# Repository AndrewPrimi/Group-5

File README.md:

# Electronics Tool Bench – Group 5

This repository is used to store coursework, scripts, and supporting materials for our electronics and embedded systems projects throughout the semester. It includes work completed using tools such as the Raspberry Pi and GitHub for collaborative development.

## Course Deliverables
 - Documentaton under Technical_Documenation Folder
 - User Manual under User_Manual folder
 - Current Status of these files are relevant to the status of the completion of the project, these files updated with every deliverable and checkpoint

### Deliverable 2 – Raspberry Pi Hello World (RP4)
- File(s): HelloWorldPI.py, HelloWorldScripts
- Description: Python script used to verify Raspberry Pi setup and GitHub integration. The script was run successfully on the Raspberry Pi as part of the assignment. Practice GitHub Commit files. 

### Deiverable 3 - DigiPot and Rotary Encoder
- File(s): gpio_status.py, gpio_status_simple.py, potentiometer.py, LED_ON_OFF.py
- Description: Scripts used to setup GPIO ports and to use the digital potentiometer (change resistance) and rotary encoder (turn off/on an LED), LED turn off and on script.

### Deliverable 4 – Power Supply Simulation, CAD, GPIO Diagram and Power Diagram
- File(s): Deliverable_4.pdf, KiCad_Files, Multisim_Schematics
- Description: GPIO and power diagrams, ±12 V power supply simulation, and initial PCB CAD design using KiCad for future Pi-HAT development.

### Deliverable 5 – Checkpoint C (DigiPot User Interface)  
- File(s): Checkpoint_C_Code (name your Checkpoint “C” code clearly), updated weekly documentation + demo video
- Description: Rotary encoder + LCD user interface to set and display digipot resistance. Slow spin adjusts by 10 Ω and fast spin adjusts by 100 Ω, with a selectable range of 100 Ω to 10 kΩ. Pressing the encoder selects/sets the value and programs the digipot (verified with a multimeter). The UI must allow selecting which side of the dual digipot is being controlled and each side must be independent. Holding the knob for 3 seconds returns to the primary selection screen. No LCD buttons are used and the system should not reboot between resistance changes.

### Deliverable 6 – ±12 V Supply Under Load, 5-bit ADC Simulation, and PCB Schematic Updates
- File(s): Deliverable_6.pdf, KiCad_Files, Multisim_Schematics, updated weekly documentation
- Description: Updated and validated the split-rail ±12 V power supply to ensure stability with no load and with an approximate 50 mA load on both rails. Documented and clarified system ground/reference behavior, including the virtual ground midpoint concept. Developed and simulated a 5-bit-equivalent ADC design using a SAR-based approach with an R-2R DAC, sample-and-hold circuit, and LM339 comparator. Updated the Pi-Hat protector KiCad schematic/PCB to include the ±12 V supply nets (+12 V, GND, −12 V), ADC routing concepts, and initial layout/routing screenshots with key design decisions and debugging considerations (labels, test points, footprints).

### Deliverable 7 – Physical ADC, Ohmmeter, Voltmeter
- File(s): N/A
- Description: 
  
Additional deliverables will be added to this repository as the semester progresses.

## Group Members
- Andrew Primiano  
- Logan Griffy  
- Tillman Clark  
- George Braun
- Kai DeVito

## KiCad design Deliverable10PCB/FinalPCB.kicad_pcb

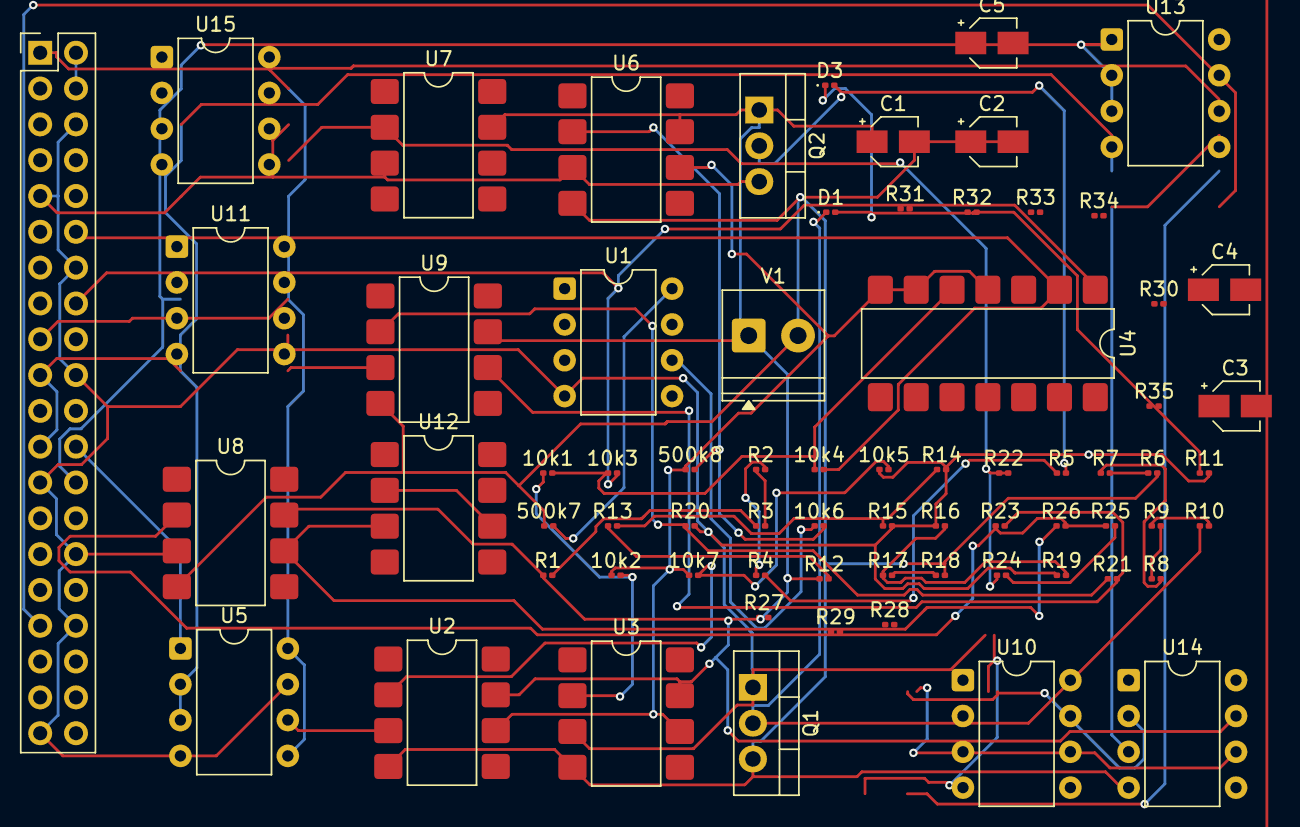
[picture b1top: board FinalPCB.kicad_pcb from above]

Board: 2 copper layers, 70 parts (0 on the bottom side), 53 nets.

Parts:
10k1, 10k2, 10k3, 10k4, 10k5, 10k6, 10k7, 500k7: R; R_0201_0603Metric
500k8: R_Measure; R_0201_0603Metric
C1, C2: 0.0000001; CP_Elec_3x5.3
C3: 470uF; CP_Elec_3x5.3
C4, C5: 10nf; CP_Elec_3x5.3
D1, D3: D; D_0201_0603Metric
J2: PiHeaderM; PinHeader_2x20_P2.54mm_Vertical
Q1: NMOS; TO-220-3_Vertical
Q2: PMOS; TO-220-3_Vertical
R1, R2, R3, R4, R5, R6, R7, R8, R9, R10, R11, R12, R13, R14, R15, R16, R17, R18, R19: 100; R_0201_0603Metric
R20, R22, R23, R25, R26, R28: 10k; R_0201_0603Metric
R21: 20k; R_0201_0603Metric
R24: 30k; R_0201_0603Metric
R27, R31, R32, R33, R34: 100k; R_0201_0603Metric
R29: 70k; R_0201_0603Metric
R30, R35: 220k; R_0201_0603Metric
U1, U5, U13: MCP4131-xxxx-P; DIP-8_W7.62mm
U2, U3, U6, U7, U8, U9, U12: LM741; SMDIP-8_W7.62mm
U4: LM339; SMDIP-14_W7.62mm
U10, U11, U14: TL081; DIP-8_W7.62mm
U15: MCP4231-103E_P; DIP-8_W7.62mm
V1: 24; TerminalBlock_Phoenix_PT-1,5-2-3.5-H_1x02_P3.50mm_Horizontal

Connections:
+3.3V: 10k1.2, U4.5 (+)
+12V: C1.1, Q2.1 (D), R1.1, R12.1, U2.7 (V+), U3.7 (V+), U6.7 (V+), U7.7 (V+), U8.7 (V+), U9.7 (V+), U10.7 (V+), U11.7 (V+), U14.7 (V+), V1.1
-12V: 500k7.1, C1.2, C2.1, C2.2, Q1.3 (S), R6.2, R18.2, U2.4 (V-), U3.4 (V-), U6.4 (V-), U8.4 (V-), U9.4 (V-), U10.4 (V-), U11.4 (V-), U14.4 (V-), V1.2
/3.3V: 10k3.1, 10k4.1, J2.1, J2.17, U13.5 (P0A), U13.8 (V_{DD}), U15.7 (P1A), U15.8 (P0A)
/5V: J2.2, J2.4
/CE0: J2.24, U13.1 (~CS), U15.1 (~CS)
/CE1: J2.26, U1.1 (~CS), U5.1 (~CS)
/GND*GPIO: J2.6, J2.9, J2.14, J2.20, J2.25, J2.30, J2.34, J2.39
/GPIO10*: J2.19, U1.3 (SDI/SDO), U5.3 (SDI/SDO), U13.3 (SDI/SDO), U15.3 (SDI)
/GPIO11*: J2.23, U1.2 (SCK), U5.2 (SCK), U13.2 (SCK), U15.2 (SCK)
/GPIO13*: C3.2, J2.33, U13.6 (P0W)
GND: 10k5.1, Q1.1 (D), Q2.3 (S), R11.2, R14.2, R15.2, R16.1, R19.1, R20.2, R27.1, R31.2, R34.2, U1.4 (V_{SS}), U3.3 (+), U5.7 (P0B), U6.3 (+), U7.3 (+), U8.3 (+), U13.4 (V_{SS}), U13.7 (P0B), U14.3 (+), U15.4 (VSS), U15.5 (P1B)
unnamed: 10k3.2, U4.1
unnamed: 10k4.2, U4.2
unnamed: C3.1, R27.2, R28.1
unnamed: C4.1, R30.2, R33.2, U10.6
unnamed: C5.1, R35.2, U11.6
unnamed: D1.2 (A), D3.1 (K), R11.1
unnamed: D1.1 (K), Q1.2 (G), R10.1
unnamed: D3.2 (A), Q2.2 (G), R5.2
unnamed: R1.2, R3.1
unnamed: R2.1, R3.2
unnamed: R2.2, R4.1
unnamed: R4.2, R5.1
unnamed: R6.1, R7.2
unnamed: R7.1, R8.2
unnamed: R8.1, R9.2
unnamed: R9.1, R10.2
unnamed: R12.2, R13.1
unnamed: R13.2, R14.1, R15.1
unnamed: R16.2, R17.1, R19.2
unnamed: R17.2, R18.1
unnamed: R21.2, R23.2, U9.6
unnamed: R24.2, R25.2
unnamed: R29.2, R32.2, U14.6
unnamed: 10k6.1, U1.6 (P0W)
unnamed: 500k7.2, U1.8 (V_{DD})
unnamed: U2.3 (+), U5.6 (P0W)
unnamed: 10k5.2, 10k7.2, U2.2 (-)
unnamed: 10k1.1, 10k2.2, U3.2 (-)
unnamed: 10k2.1, 10k7.1, 500k8.1, U2.6, U3.6, U4.4 (-), U4.6 (-), U4.7 (+), U6.6
unnamed: U5.5 (P0A), U5.8 (V_{DD})
unnamed: 10k6.2, 500k8.2, U6.2 (-)
unnamed: R23.1, R25.1, R26.2, U8.2 (-)
unnamed: R20.1, R21.1, U9.2 (-)
unnamed: R31.1, U10.3 (+)
unnamed: C4.2, R30.1, R32.1, U10.2 (-)
unnamed: R34.1, U11.3 (+)
unnamed: C5.2, R33.1, R35.1, U11.2 (-)
unnamed: R26.1, U8.6, U12.3 (+)
unnamed: U12.2 (-), U12.6
unnamed: R28.2, R29.1, U14.2 (-)
unnamed: R22.1, R22.2, R24.1, U7.2 (-), U15.6 (P1W)

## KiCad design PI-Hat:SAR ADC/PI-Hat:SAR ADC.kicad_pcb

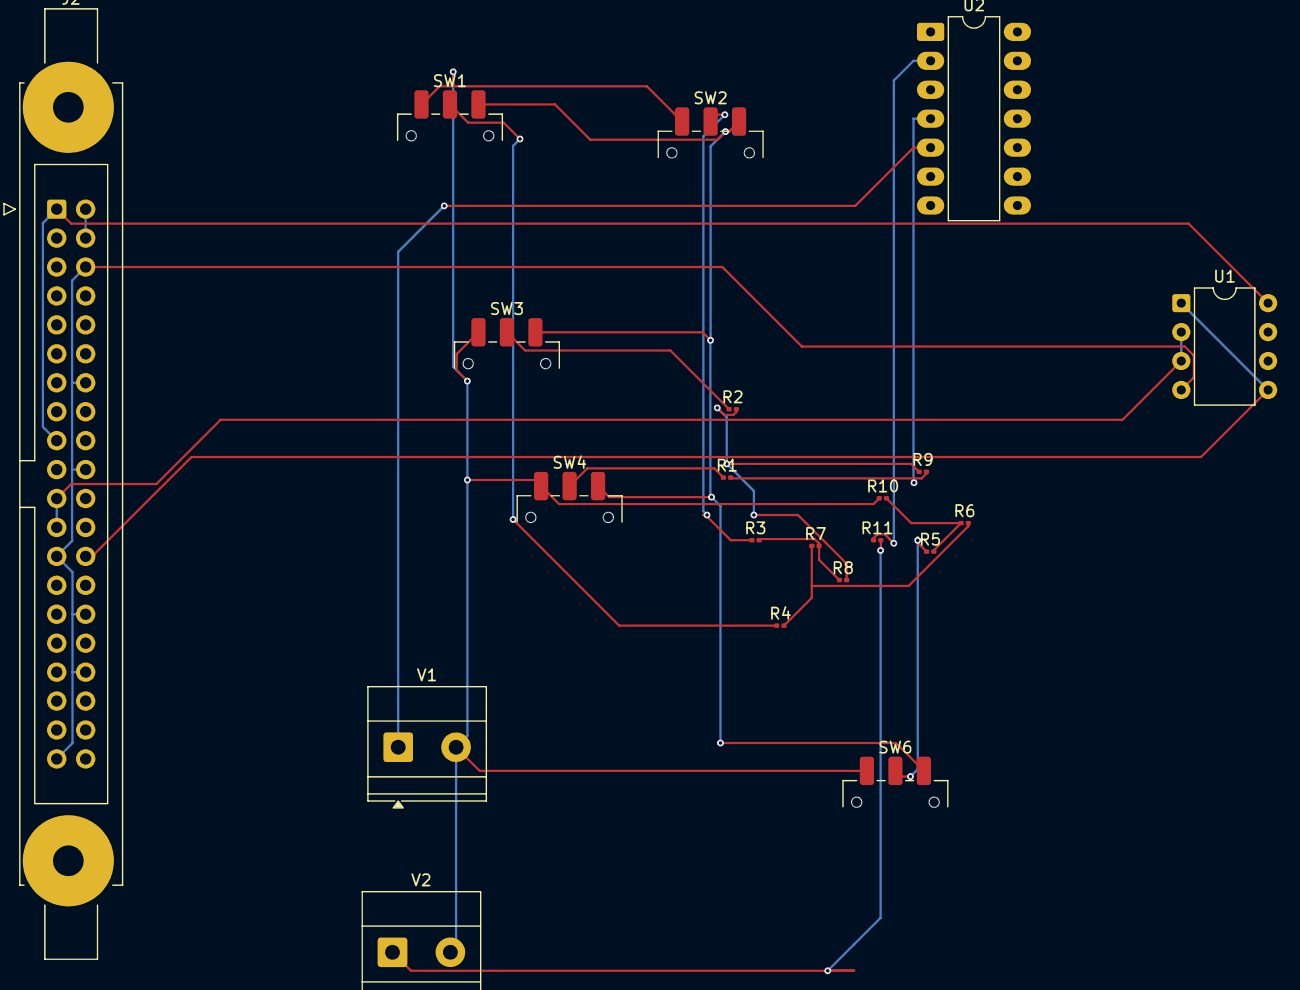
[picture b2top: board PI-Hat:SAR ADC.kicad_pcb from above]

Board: 2 copper layers, 21 parts (0 on the bottom side), 20 nets.

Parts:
J2: PiHeaderM; IDC-Header_2x20-1MP_P2.54mm_Latch6.5mm_Vertical
R1, R2, R3, R4, R5, R10: 200; R_0201_0603Metric
R6, R7, R8, R9: 100; R_0201_0603Metric
R11: 10k; R_0201_0603Metric
SW1: Key = 2; SW_SPDT_CK_JS102011SAQN
SW2: Key = 3; SW_SPDT_CK_JS102011SAQN
SW3: Key = 4; SW_SPDT_CK_JS102011SAQN
SW4: Key = 5; SW_SPDT_CK_JS102011SAQN
SW6: Key = 1; SW_SPDT_CK_JS102011SAQN
U1: MCP4131-xxxx-P; DIP-8_W7.62mm
U2: LM339; DIP-14_W7.62mm_LongPads
V1: 1; TerminalBlock_Phoenix_MKDS-1,5-2-5.08_1x02_P5.08mm_Horizont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
V2: 1.7; TerminalBlock_Phoenix_MKDS-1,5-2-5.08_1x02_P5.08mm_Horizont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

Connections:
+5V: SW1.3 (C), SW2.3 (C), SW3.3 (C), SW4.3 (C), SW6.3 (C)
/3V3GPIO*: J2.1, J2.17, U1.8 (V_{DD})
/5VGPIO*: J2.2, J2.4
/GND*GPIO: J2.6, J2.14, J2.20, J2.25, J2.30, J2.34, J2.39, U1.4 (V_{SS})
/GPIO7*: J2.26, U1.1 (~CS), U1.5 (P0A)
/GPIO11*: J2.21, J2.23, U1.2 (SCK), U1.3 (SDI/SDO)
GND: R10.1, SW1.1 (A), SW2.1 (A), SW3.1 (A), SW4.1 (A), SW6.1 (A), V1.2, V2.2
unnamed: R2.2, R8.2, R9.1
unnamed: R3.2, R7.2, R8.1
unnamed: R4.2, R6.2, R7.1
unnamed: R5.2, R6.1, R10.2
unnamed: R11.1, U2.2
unnamed: R11.2, V2.1
unnamed: R4.1, SW1.2 (B)
unnamed: R3.1, SW2.2 (B)
unnamed: R2.1, SW3.2 (B)
unnamed: R1.1, SW4.2 (B)
unnamed: R5.1, SW6.2 (B)
unnamed: U2.5 (+), V1.1
unnamed: R1.2, R9.2, U2.4 (-)

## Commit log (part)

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2026-03-17 copied public deliverable 5 into private repo
2026-03-17 back to normal
2026-03-17 fix rotary
2026-03-18 digipots save value
2026-03-18 getting better digi pot values
2026-03-20 fix lcd bugs
2026-03-21 Deliverable_7 Driver
2026-03-21 Deliverable_7 i2c_lcd
2026-03-21 Deliverable_7 i2c_lcd and Driver
2026-03-21 ohmmeter.py
2026-03-21 ohmmeter.py and Driver
2026-03-21 fixing bugs that did not exist 2 days ago
2026-03-21 i2c lcd is still glitching
2026-03-21 Update i2c_lcd.py 0x27
2026-03-21 Update i2c_lcd.py 0x26
2026-03-21 Update i2c_lcd.py 0x25
2026-03-21 Update i2c_lcd.py 0x24
2026-03-21 Update i2c_lcd.py None
2026-03-21 Update i2c_lcd.py changed init
2026-03-21 update i2c_lcd
2026-03-21 temporary ui bec lcd does not work
2026-03-21 changes for cmd_driver
2026-03-21 goddammit
2026-03-21 sucks our lcd doesnt work
2026-03-21 stopping...
2026-03-21 digipot spi 1
2026-03-21 gonna fix the ohms steps thing now
2026-03-21 fixed volt meter
2026-03-21 dictionary digipot
2026-03-21 Revert "Replace voltmeter formula with calibration lookup table"
    This reverts commit dc97782d2454f2300795cdafdacc6606d5bcb785.
2026-03-21 fix ohms_steps stuff
2026-03-21 ohms steps
2026-03-22 pot1
2026-03-22 yay we figured out the ohmmeter and voltmeter so kai is finishing up the transfer function for the pots
2026-03-22 Update ohms_steps.py to do interpolation with a dictionary
2026-03-22 checkpoint-b callbacks WIP
2026-03-22 steps in driver
2026-03-23 fixed square meter
2026-03-23 checkpoint b ui is complete
2026-03-23 checkpoint b ui
2026-03-24 started over on ui and just pot should work
2026-03-24 started over on ui for b
2026-03-24 moved sqaure_wave.py to Del9
2026-03-24 cleaned up Deliverable 9
2026-03-24 fixed the rotation on the ui
2026-03-24 fixed voltmeter.py
2026-03-24 fixed ui text
2026-03-24 added ui changes
2026-03-24 fixed voltmeter
2026-03-24 fix ohmmeter
2026-03-24 fixed ohmmeter
2026-03-25 added voltmeter
2026-03-25 added turn off feature
2026-03-25 simple change
2026-03-25 added 8
2026-04-06 changed steps at pos
2026-04-06 sine wave using pwm
2026-04-06 mock ui for sinewave
2026-04-06 sinewave ui
2026-04-06 fixed sinewave
2026-04-06 sine wave measurer
2026-04-06 sine wave measures frequency
2026-04-07 fix 1
2026-04-07 fix 2
2026-04-07 fix 3
2026-04-07 changed freq increments
2026-04-08 sine measurement ui
2026-04-10 comments
2026-04-14 ui changes
2026-04-14 Ohmmeter
2026-04-14 sinwave
2026-04-19 included comments for tech doc
